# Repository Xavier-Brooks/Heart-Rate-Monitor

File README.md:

# Heart-Rate-Monitor
Designed a  simple Heart Rate monitor PCB

Below You'll find the schematic design for the HRM which contains errors - so be warned

Below is a picture of the board for the HRM 

both files can be submitted to OSHPark and similar sites if you want the PCB ordered online 
This design was done as part of a class and my first attempt at PCB design so it's not the best. I'm open for recommendation if your intrigued by the design.

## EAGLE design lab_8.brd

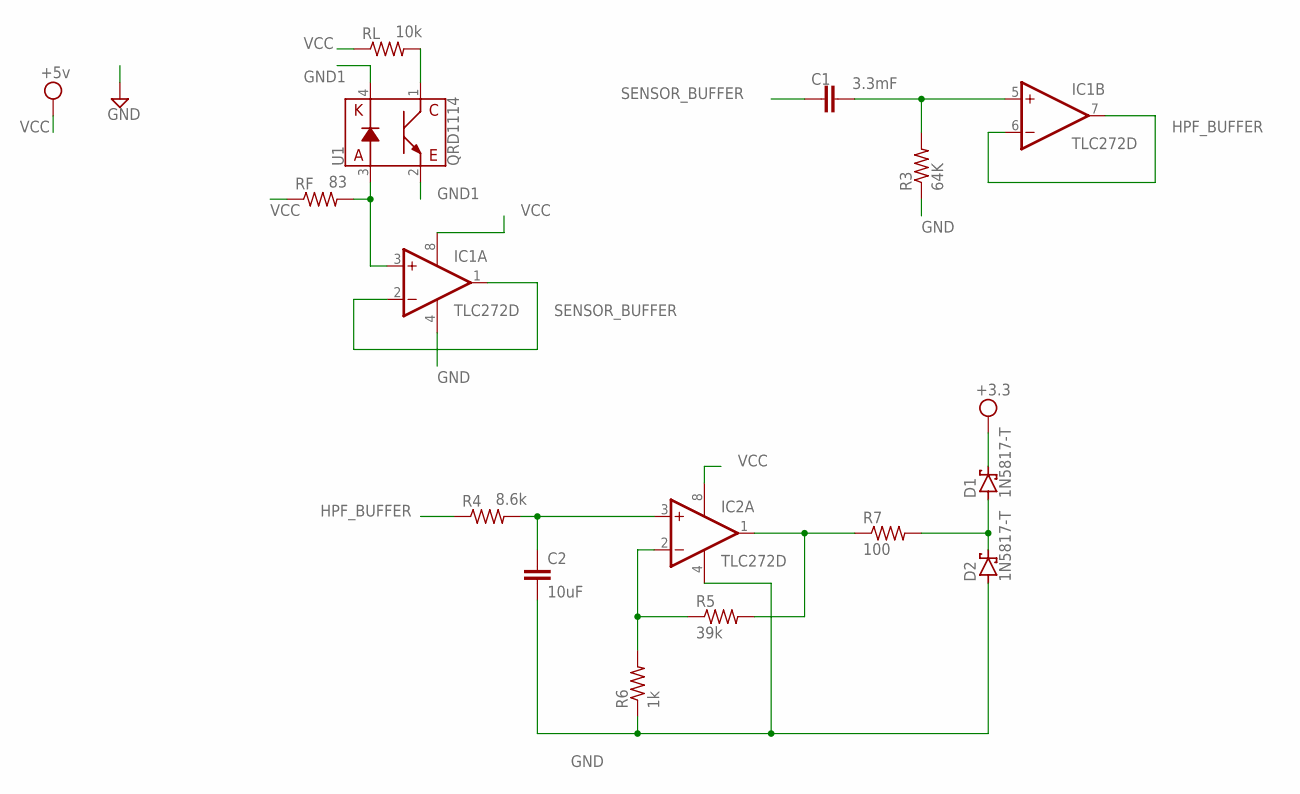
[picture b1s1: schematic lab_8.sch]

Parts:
C1: 3.3mF; C025-025X050
C2: 10uF; C025-025X050
D1, D2: 1N5817-T; DO41-7.6
IC1, IC2: TLC272D; SO08
R3: 64K; R0805
R4: 8.6k; R0805
R5: 39k; R0805
R6: 1k; R0805
R7: 100; R0805
RF: 83; R0805
RL: 10k; R0805
U1: QRD1114

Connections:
GND: C2.2, D2.A, IC1.4 (V-), IC2.4 (V-), R3.1, R6.1
GND1: U1.2 (E), U1.4 (K)
HPF_BUFFER: IC1.6 (-IN), IC1.7 (OUT), R4.1
unnamed: C1.2, IC1.5 (+IN), R3.2
unnamed: C2.1, IC2.3 (+IN), R4.2
unnamed: IC1.3 (+IN), RF.2, U1.3 (A)
unnamed: IC2.2 (-IN), R5.1, R6.2
unnamed: IC2.1 (OUT), R5.2, R7.1
unnamed: D1.A, D2.C, R7.2
SENSOR_BUFFER: C1.1, IC1.1 (OUT), IC1.2 (-IN)
VCC: D1.C, IC1.8 (V+), IC2.8 (V+), RF.1, RL.1, RL.2, U1.1 (C)

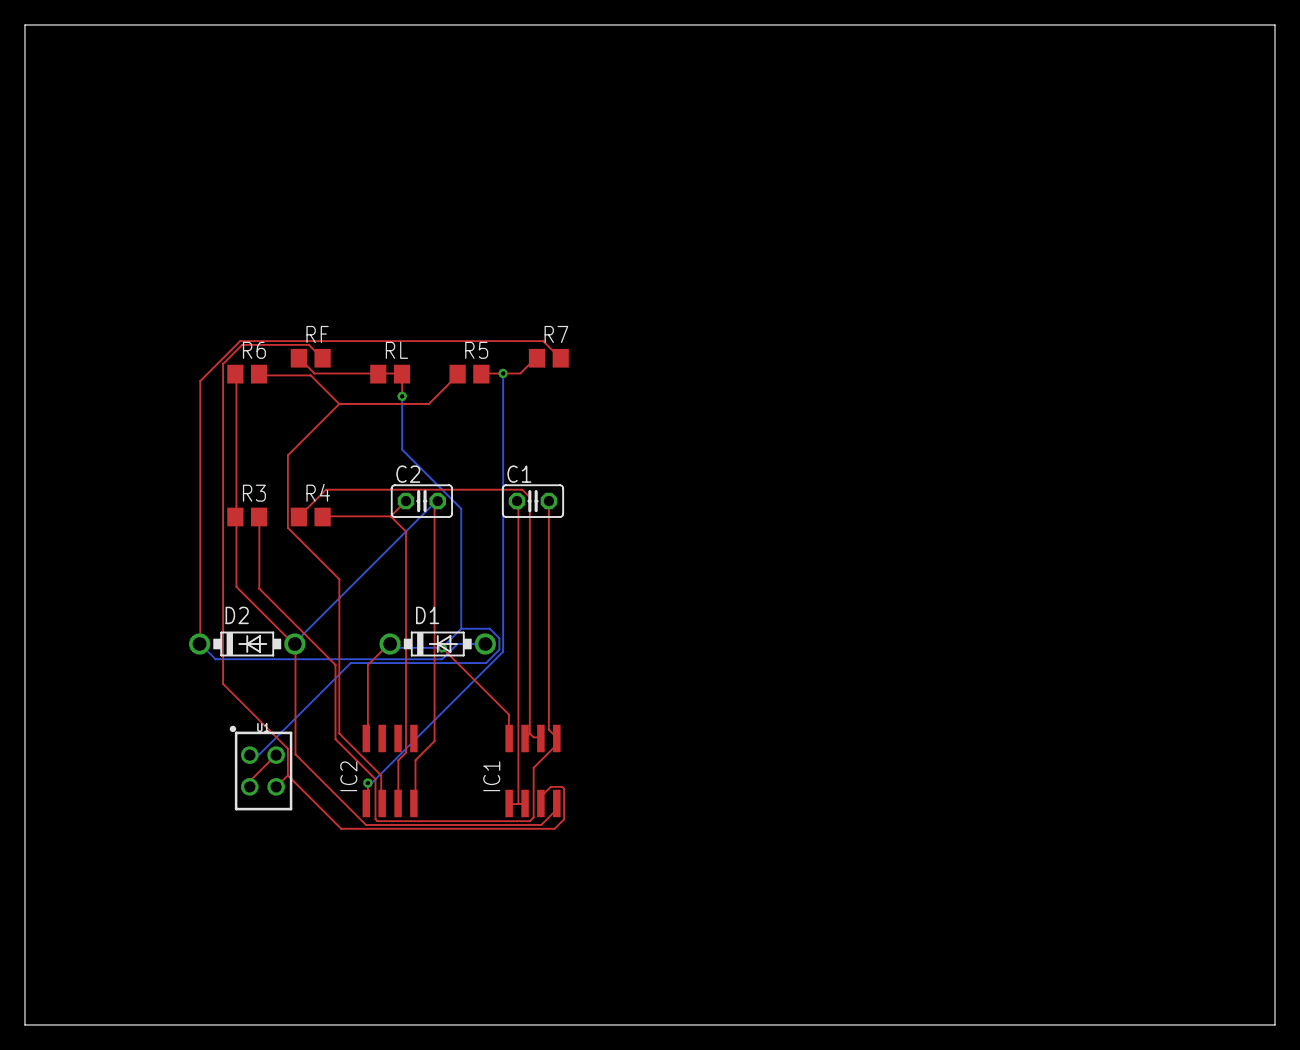
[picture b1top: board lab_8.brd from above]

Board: 2 copper layers, 100.0 x 80.0 mm, 14 parts (0 on the bottom side), 11 nets.

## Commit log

2020-12-14 Add files via upload
    contains the schematic and board design for the heart rate monitor
2020-12-14 Add files via upload
    schematic picture
2020-12-14 Add files via upload
    board picture
2020-12-14 Update README.md
    pictures added to the README.md

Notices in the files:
parts and their libraries:
SparkFun-Sensors: Licensing: Creative Commons ShareAlike 4.0 International - https://creativecommons.org/licenses/by-sa/4.0
